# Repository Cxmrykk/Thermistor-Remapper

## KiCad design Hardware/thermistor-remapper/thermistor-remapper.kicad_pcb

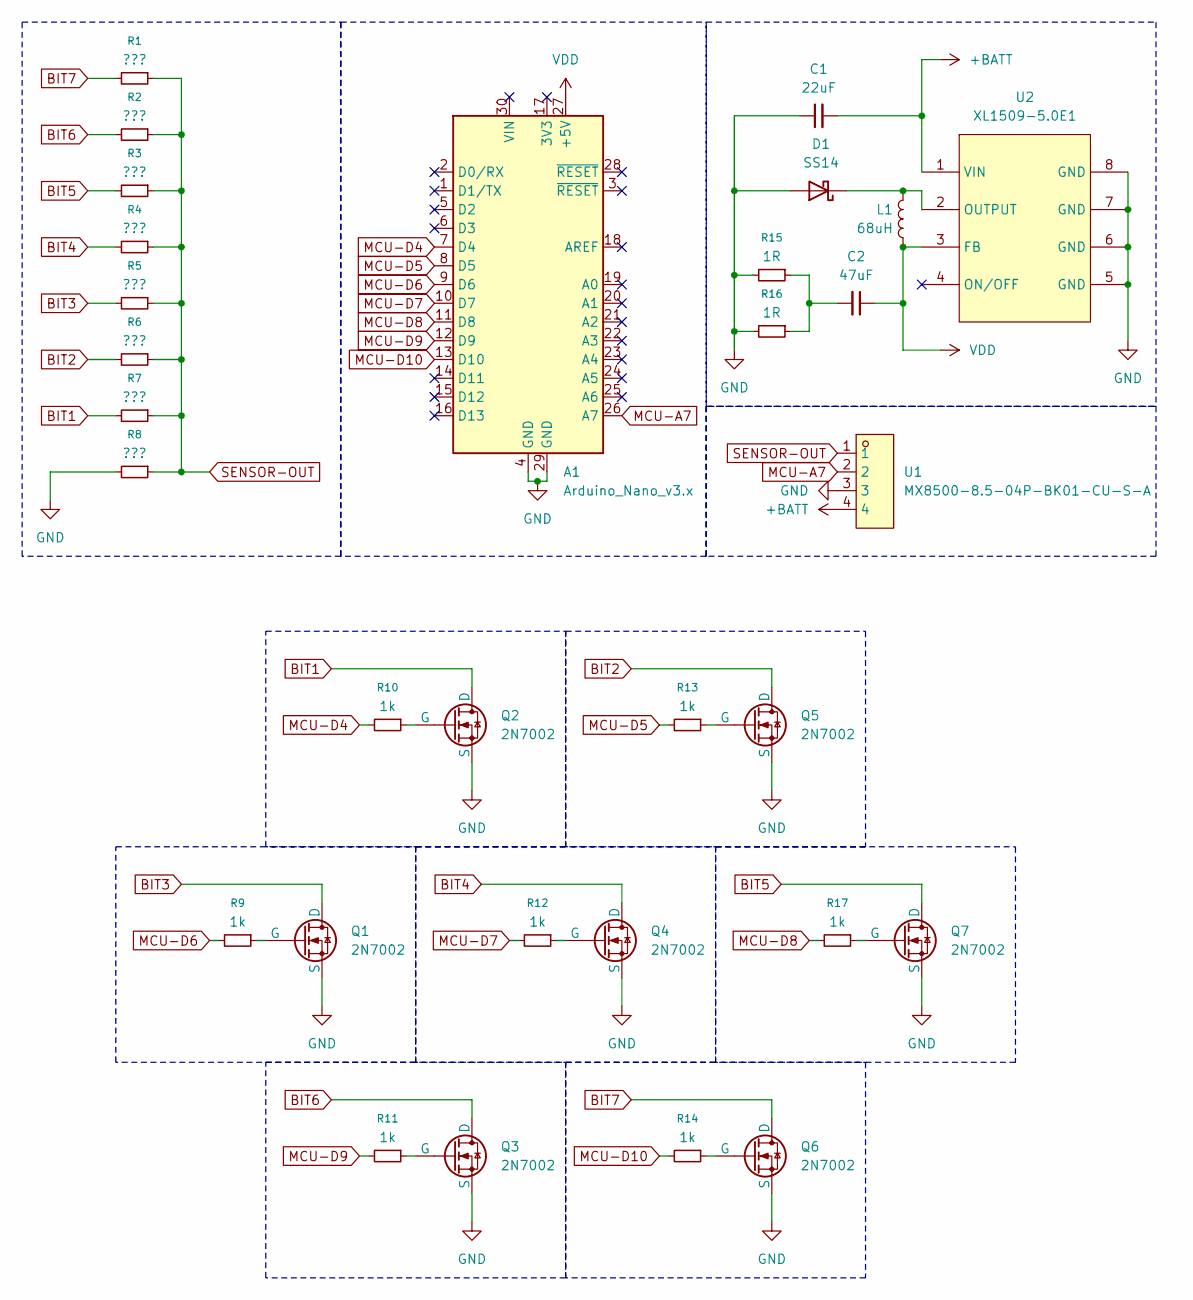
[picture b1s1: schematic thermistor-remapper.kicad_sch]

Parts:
A1: Arduino_Nano_v3.x; Arduino_Nano
C1: 22uF; C_1206_3216Metric_Pad1.33x1.80mm_HandSolder
C2: 47uF; C_1206_3216Metric_Pad1.33x1.80mm_HandSolder
D1: SS14; D_SMA_Handsoldering
L1: 68uH; L_Bourns_SRN6045TA
Q1, Q2, Q3, Q4, Q5, Q6, Q7: 2N7002; SOT-23_Handsoldering
R1, R2, R3, R4, R5, R6, R7, R8: ???; R_0805_2012Metric_Pad1.20x1.40mm_HandSolder
R9, R10, R11, R12, R13, R14, R17: 1k; R_0805_2012Metric_Pad1.20x1.40mm_HandSolder
R15, R16: 1R; R_0805_2012Metric_Pad1.20x1.40mm_HandSolder
U1: MX8500-8.5-04P-BK01-CU-S-A; CONN-TH_4P-P8.50_MX8500-8.5-04P-GN01-CU-S-A; LCSC Part C5188508
U2: XL1509-5.0E1; SOIC-8_L5.0-W4.0-P1.27-LS6.0-BL; LCSC Part C61063

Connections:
+BATT: C1.2, U1.4, U2.1 (VIN)
BIT1: Q2.3 (D), R7.2
BIT2: Q5.3 (D), R6.2
BIT3: Q1.3 (D), R5.2
BIT4: Q4.3 (D), R4.2
BIT5: Q7.3 (D), R3.2
BIT6: Q3.3 (D), R2.2
BIT7: Q6.3 (D), R1.2
GND: A1.4 (GND), A1.29 (GND), C1.1, D1.2 (A), Q1.2 (S), Q2.2 (S), Q3.2 (S), Q4.2 (S), Q5.2 (S), Q6.2 (S), Q7.2 (S), R8.2, R15.2, R16.2, U1.3, U2.5 (GND), U2.6 (GND), U2.7 (GND), U2.8 (GND)
MCU-A7: A1.26 (A7), U1.2
MCU-D4: A1.7 (D4), R10.2
MCU-D5: A1.8 (D5), R13.2
MCU-D6: A1.9 (D6), R9.2
MCU-D7: A1.10 (D7), R12.2
MCU-D8: A1.11 (D8), R17.2
MCU-D9: A1.12 (D9), R11.2
MCU-D10: A1.13 (D10), R14.2
unnamed: C2.2, R15.1, R16.1
unnamed: D1.1 (K), L1.1, U2.2 (OUTPUT)
unnamed: Q1.1 (G), R9.1
unnamed: Q2.1 (G), R10.1
unnamed: Q3.1 (G), R11.1
unnamed: Q4.1 (G), R12.1
unnamed: Q5.1 (G), R13.1
unnamed: Q6.1 (G), R14.1
unnamed: Q7.1 (G), R17.1
SENSOR-OUT: R1.1, R2.1, R3.1, R4.1, R5.1, R6.1, R7.1, R8.1, U1.1
VDD: A1.27 (+5V), C2.1, L1.2, U2.3 (FB)

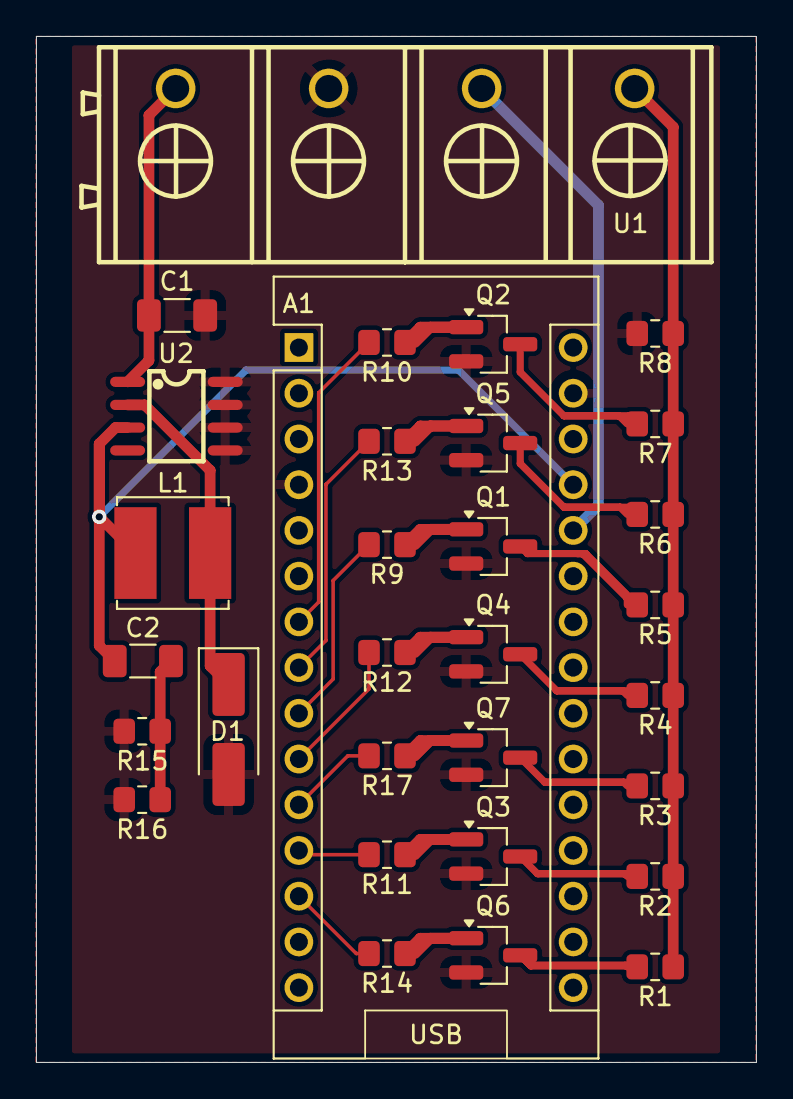
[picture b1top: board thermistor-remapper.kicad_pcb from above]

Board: 2 copper layers, 40.0 x 57.0 mm, 31 parts (0 on the bottom side), 28 nets.

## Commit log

2025-12-14 Add .gitignore
2025-12-15 Add hardware
2025-12-15 Schematic + PCB
2025-12-16 Completed prototype
2025-12-16 Remove and ignore backups
2025-12-16 Change resistors to 0806
2025-12-16 Remove unused files
2026-01-04 Upload firmware template
2026-01-04 Use new firmware upload speed
2026-01-04 Provide instructions for upload failure
